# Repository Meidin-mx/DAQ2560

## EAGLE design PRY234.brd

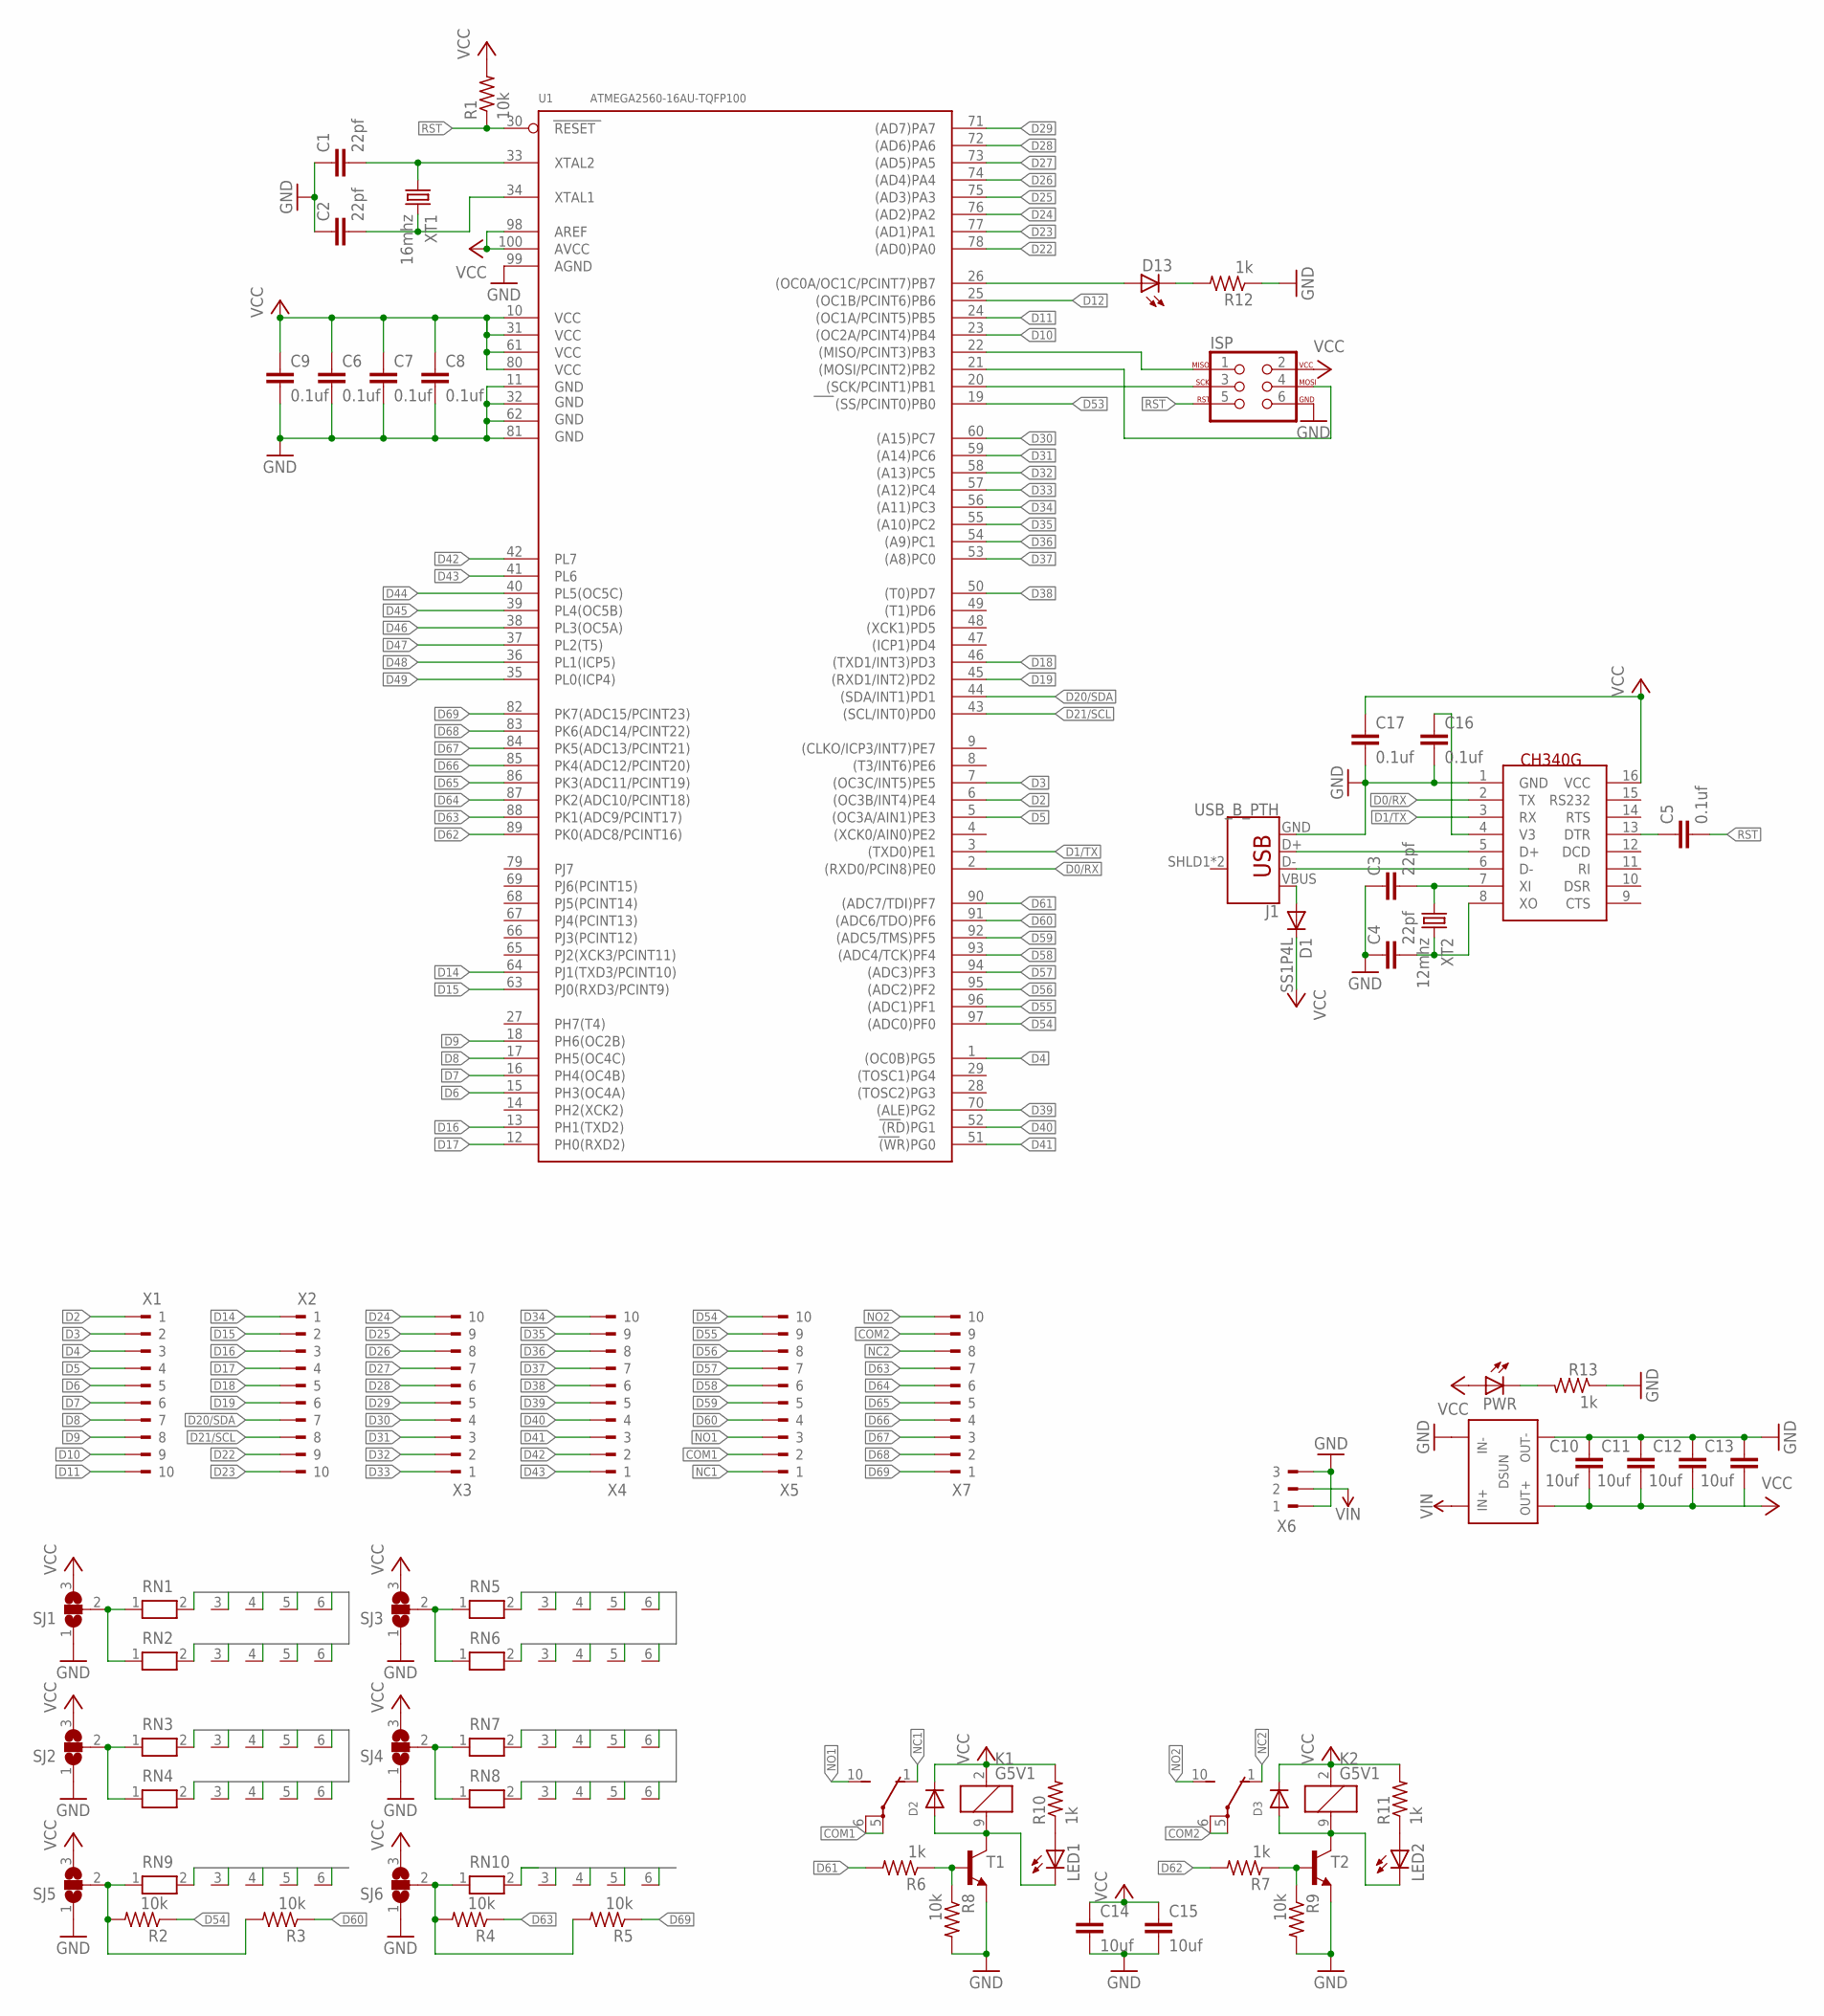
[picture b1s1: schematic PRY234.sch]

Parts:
C1, C2, C3, C4: 22pf; C0805
C5, C6, C7, C8, C9, C16, C17: 0.1uf; C0805
C10, C11, C12, C13, C14, C15: 10uf; C0805
D1: SS1P4L; DO220AAL
D2, D3: DIODESOD-323F; SOD-323F
D13: LEDCHIPLED_0805; CHIPLED_0805
ISP: AVR_SPI_PROG_3X2PTH; 2X3
J1: USB_B_PTH; USB-B-PTH
K1, K2: G5V1
LED1, LED2: LEDCHIPLED_0805; CHIPLED_0805
PWR: LEDCHIPLED_0805; CHIPLED_0805
R1, R2, R3, R4, R5, R8, R9: 10k; M0805
R6, R7, R10, R11, R12, R13: 1k; M0805
RN1, RN2, RN3, RN4, RN5, RN6, RN7, RN8, RN9, RN10: RN05; RN-6
SJ1, SJ2, SJ3, SJ4, SJ5, SJ6: SJ2W; SJ_2
T1, T2: MMBT2222ALT1-NPN-SOT23-BEC; SOT23-BEC
U1: ATMEGA2560-16AU-TQFP100; TQFP100-0.5-14X14MM
U$1: CH340G; SOIC16
U$3: DSUN
X1, X2, X3, X4, X5, X7: 90-10
X6: 90-3
XT1: 16mhz; XTAL7641
XT2: 12mhz; XTAL7641

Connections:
COM1: K1.5, K1.6, X5.2
COM2: K2.5, K2.6, X7.9
D0/RX: U1.2 ((RXD0/PCIN8)PE0), U$1.2 (TX)
D1/TX: U1.3 ((TXD0)PE1), U$1.3 (RX)
D2: RN1.6, U1.6 ((OC3B/INT4)PE4), X1.1
D3: RN1.5, U1.7 ((OC3C/INT5)PE5), X1.2
D4: RN1.4, U1.1 ((OC0B)PG5), X1.3
D5: RN1.3, U1.5 ((OC3A/AIN1)PE3), X1.4
D6: RN1.2, U1.15 (PH3(OC4A)), X1.5
D7: RN2.2, U1.16 (PH4(OC4B)), X1.6
D8: RN2.3, U1.17 (PH5(OC4C)), X1.7
D9: RN2.4, U1.18 (PH6(OC2B)), X1.8
D10: RN2.5, U1.23 ((OC2A/PCINT4)PB4), X1.9
D11: RN2.6, U1.24 ((OC1A/PCINT5)PB5), X1.10
D12: U1.25 ((OC1B/PCINT6)PB6)
D14: RN3.6, U1.64 (PJ1(TXD3/PCINT10)), X2.1
D15: RN3.5, U1.63 (PJ0(RXD3/PCINT9)), X2.2
D16: RN3.4, U1.13 (PH1(TXD2)), X2.3
D17: RN3.3, U1.12 (PH0(RXD2)), X2.4
D18: RN3.2, U1.46 ((TXD1/INT3)PD3), X2.5
D19: RN4.2, U1.45 ((RXD1/INT2)PD2), X2.6
D20/SDA: RN4.3, U1.44 ((SDA/INT1)PD1), X2.7
D21/SCL: RN4.4, U1.43 ((SCL/INT0)PD0), X2.8
D22: RN4.5, U1.78 ((AD0)PA0), X2.9
D23: RN4.6, U1.77 ((AD1)PA1), X2.10
D24: RN5.6, U1.76 ((AD2)PA2), X3.10
D25: RN5.5, U1.75 ((AD3)PA3), X3.9
D26: RN5.4, U1.74 ((AD4)PA4), X3.8
D27: RN5.3, U1.73 ((AD5)PA5), X3.7
D28: RN5.2, U1.72 ((AD6)PA6), X3.6
D29: RN6.2, U1.71 ((AD7)PA7), X3.5
D30: RN6.3, U1.60 ((A15)PC7), X3.4
D31: RN6.4, U1.59 ((A14)PC6), X3.3
D32: RN6.5, U1.58 ((A13)PC5), X3.2
D33: RN6.6, U1.57 ((A12)PC4), X3.1
D34: RN7.6, U1.56 ((A11)PC3), X4.10
D35: RN7.5, U1.55 ((A10)PC2), X4.9
D36: RN7.4, U1.54 ((A9)PC1), X4.8
D37: RN7.3, U1.53 ((A8)PC0), X4.7
D38: RN7.2, U1.50 ((T0)PD7), X4.6
D39: RN8.2, U1.70 ((ALE)PG2), X4.5
D40: RN8.3, U1.52 ((RD)PG1), X4.4
D41: RN8.4, U1.51 ((WR)PG0), X4.3
D42: RN8.5, U1.42 (PL7), X4.2
D43: RN8.6, U1.41 (PL6), X4.1
D44: U1.40 (PL5(OC5C))
D45: U1.39 (PL4(OC5B))
D46: U1.38 (PL3(OC5A))
D47: U1.37 (PL2(T5))
D48: U1.36 (PL1(ICP5))
D49: U1.35 (PL0(ICP4))
D53: U1.19 ((SS/PCINT0)PB0)
D54: R2.1, U1.97 ((ADC0)PF0), X5.10
D55: RN9.6, U1.96 ((ADC1)PF1), X5.9
D56: RN9.5, U1.95 ((ADC2)PF2), X5.8
D57: RN9.4, U1.94 ((ADC3)PF3), X5.7
D58: RN9.3, U1.93 ((ADC4/TCK)PF4), X5.6
D59: RN9.2, U1.92 ((ADC5/TMS)PF5), X5.5
D60: R3.1, U1.91 ((ADC6/TDO)PF6), X5.4
D61: R6.2, U1.90 ((ADC7/TDI)PF7)
D62: R7.2, U1.89 (PK0(ADC8/PCINT16))
D63: R4.1, U1.88 (PK1(ADC9/PCINT17)), X7.7
D64: RN10.2, U1.87 (PK2(ADC10/PCINT18)), X7.6
D65: RN10.3, U1.86 (PK3(ADC11/PCINT19)), X7.5
D66: RN10.4, U1.85 (PK4(ADC12/PCINT20)), X7.4
D67: RN10.5, U1.84 (PK5(ADC13/PCINT21)), X7.3
D68: RN10.6, U1.83 (PK6(ADC14/PCINT22)), X7.2
D69: R5.1, U1.82 (PK7(ADC15/PCINT23)), X7.1
GND: C1.1, C2.1, C3.1, C4.1, C6.2, C7.2, C8.2, C9.2, C10.1, C11.1, C12.1, C13.1, C14.2, C15.2, C16.2, C17.2, ISP.6, J1.GND, R8.2, R9.2, R12.1, R13.1, SJ1.1, SJ2.1, SJ3.1, SJ4.1, SJ5.1, SJ6.1, T1.E, T2.E, U1.11 (GND), U1.32 (GND1), U1.62 (GND2), U1.81 (GND3), U1.99 (AGND), U$1.1 (GND), U$3.IN-@1 (IN-), U$3.OUT-@1 (OUT-), X6.1, X6.3
MISO: ISP.1, U1.22 ((MISO/PCINT3)PB3)
MOSI: ISP.4, U1.21 ((MOSI/PCINT2)PB2)
unnamed: J1.D+, U$1.5 (D+)
unnamed: RN1.1, RN2.1, SJ1.2
unnamed: RN3.1, RN4.1, SJ2.2
unnamed: J1.D-, U$1.6 (D-)
unnamed: D1.P$2 (A), J1.VBUS
unnamed: RN5.1, RN6.1, SJ3.2
unnamed: RN7.1, RN8.1, SJ4.2
unnamed: C3.2, U$1.7 (XI), XT2.1
unnamed: C4.2, U$1.8 (XO), XT2.2
unnamed: C5.1, U$1.13 (DTR)
unnamed: C1.2, U1.33 (XTAL2), XT1.1
unnamed: C2.2, U1.34 (XTAL1), XT1.2
unnamed: D2.A, K1.9 (2), LED1.C, T1.C
unnamed: D3.A, K2.9 (2), LED2.C, T2.C
unnamed: R4.2, R5.2, RN10.1, SJ6.2
unnamed: R2.2, R3.2, RN9.1, SJ5.2
unnamed: LED1.A, R10.1
unnamed: R7.1, R9.1, T2.B
unnamed: LED2.A, R11.1
unnamed: R6.1, R8.1, T1.B
unnamed: D13.C, R12.2
unnamed: D13.A, U1.26 ((OC0A/OC1C/PCINT7)PB7)
unnamed: PWR.C, R13.2
unnamed: C16.1, U$1.4 (V3)
NC1: K1.1 (O), X5.1
NC2: K2.1 (O), X7.8
NO1: K1.10 (S), X5.3
NO2: K2.10 (S), X7.10
RST: C5.2, ISP.5, R1.1, U1.30 (RESET)
SCK: ISP.3, U1.20 ((SCK/PCINT1)PB1)
VCC: C6.1, C7.1, C8.1, C9.1, C10.2, C11.2, C12.2, C13.2, C14.1, C15.1, C17.1, D1.P$1 (C), D2.C, D3.C, ISP.2, K1.2 (1), K2.2 (1), PWR.A, R1.2, R10.2, R11.2, SJ1.3, SJ2.3, SJ3.3, SJ4.3, SJ5.3, SJ6.3, U1.10 (VCC), U1.31 (VCC1), U1.61 (VCC2), U1.80 (VCC3), U1.98 (AREF), U1.100 (AVCC), U$1.16 (VCC), U$3.OUT+@2 (OUT+)
VIN: U$3.IN+@2 (IN+), X6.2

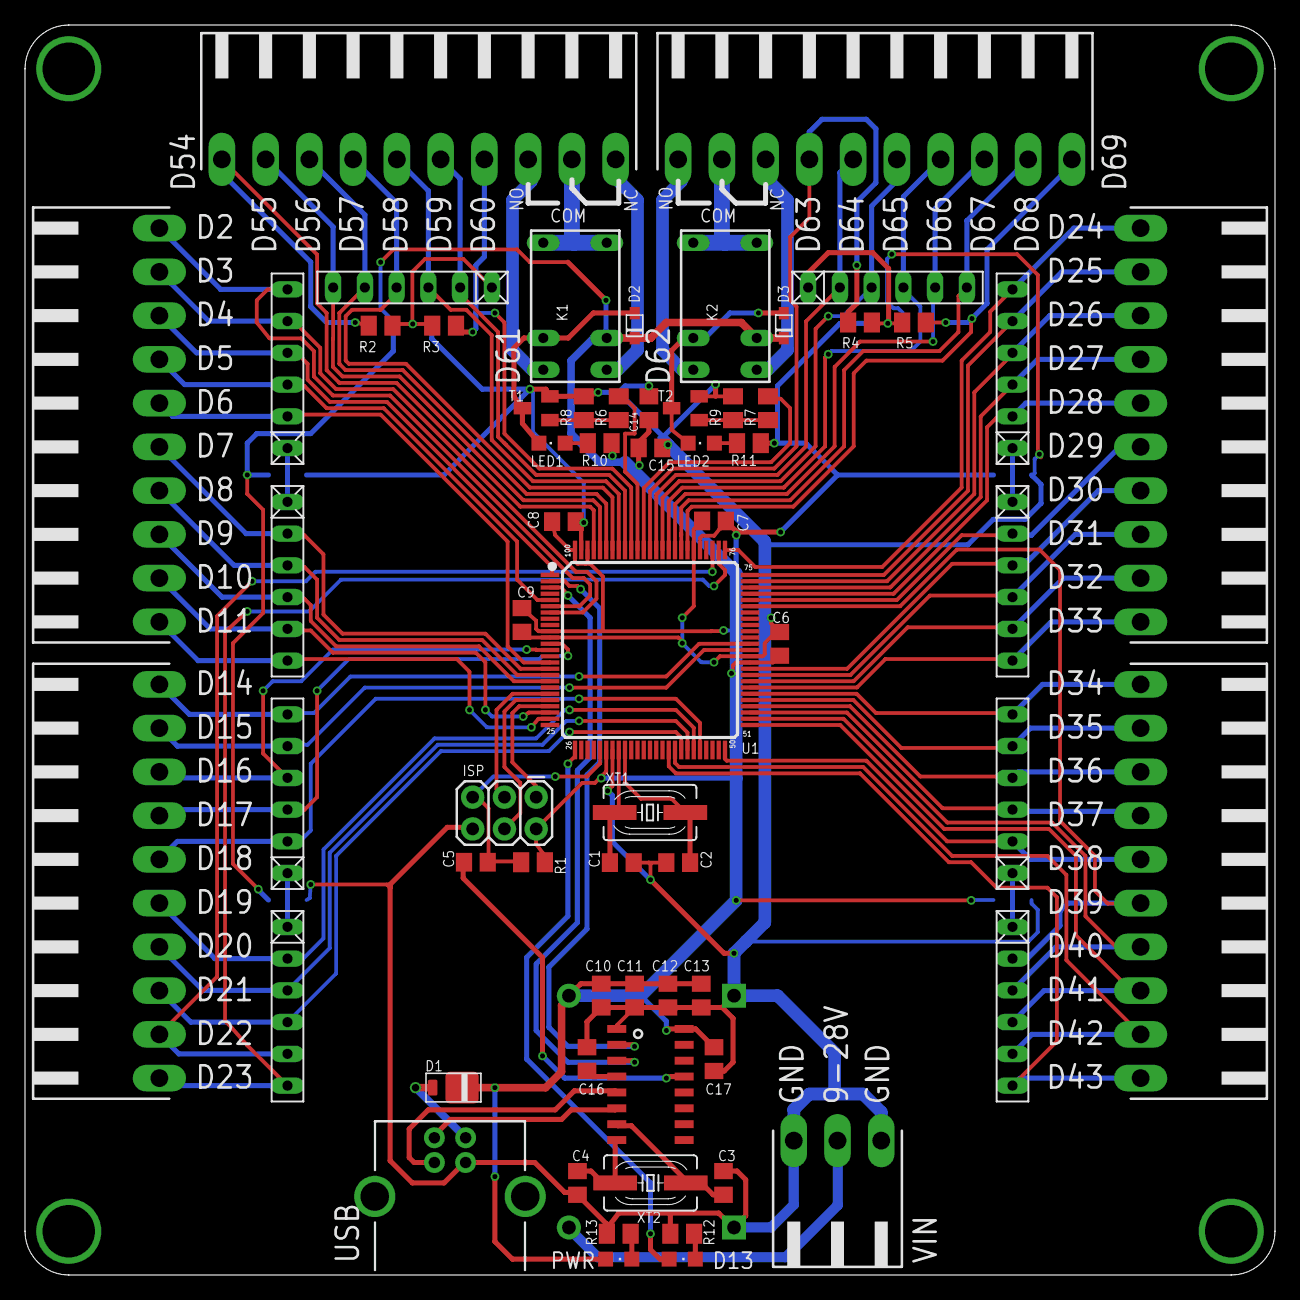
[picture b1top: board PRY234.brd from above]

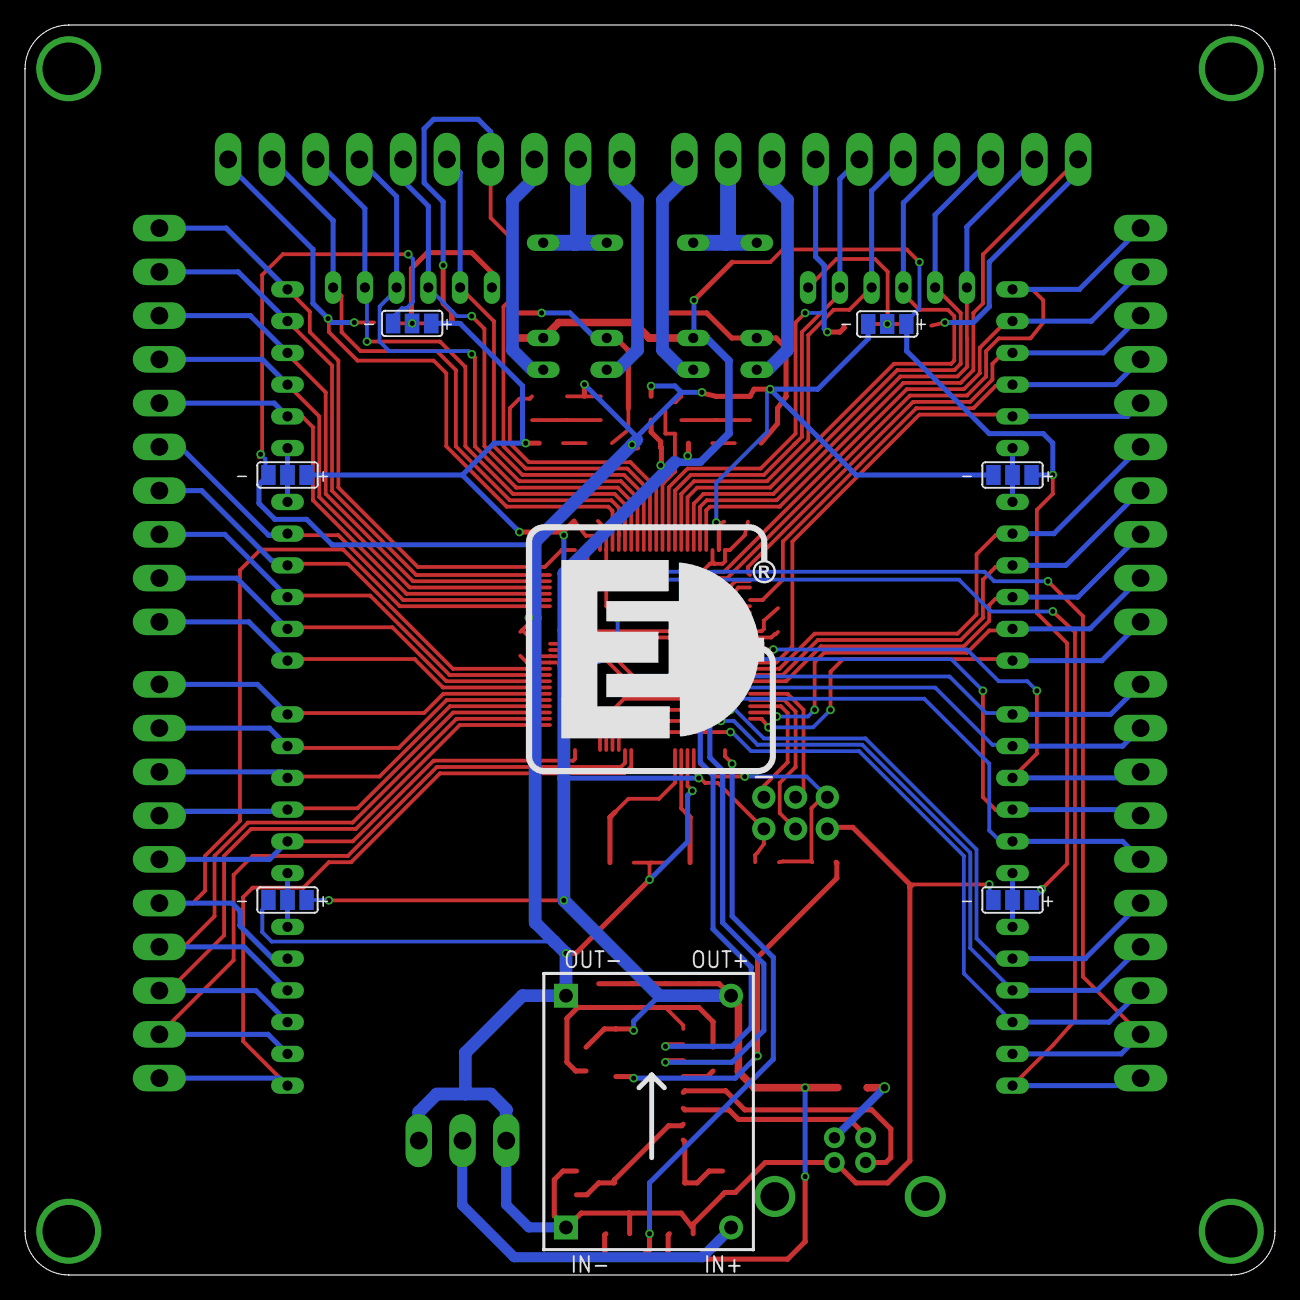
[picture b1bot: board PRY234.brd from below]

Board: 2 copper layers, 100.0 x 100.0 mm, 71 parts (7 on the bottom side), 95 nets.

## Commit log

2017-10-16 Primer

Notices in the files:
parts and their libraries:
SparkFun-Connectors: Licensing: Creative Commons ShareAlike 4.0 International - https://creativecommons.org/licenses/by-sa/4.0
